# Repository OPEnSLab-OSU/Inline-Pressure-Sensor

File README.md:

# Inline-Pressure-Sensor

[Open Science Framework](https://osf.io/2mx4a/)

Code and hardware files for the inline pressure sensor

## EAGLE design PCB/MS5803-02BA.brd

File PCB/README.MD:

# PCB Files

This folder contains all the files that are necessary for ordering the PCB.

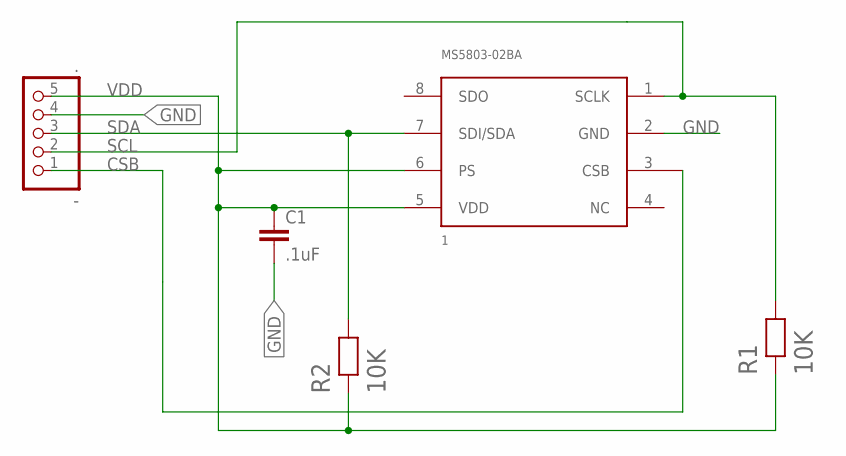
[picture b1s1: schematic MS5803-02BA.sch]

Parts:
-: .; 1X05
C1: .1uF; C0805
MS5803-02BA: 1; MS5803-02BA
R1, R2: 10K; 2012(0805)RESISTOR

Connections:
CSB: -.1, MS5803-02BA.3 (CSB)
GND: -.4, C1.2, MS5803-02BA.2 (GND)
SCL: -.2, MS5803-02BA.1 (SCLK), R1.2
SDA: -.3, MS5803-02BA.7 (SDI/SDA), R2.2
VDD: -.5, C1.1, MS5803-02BA.5 (VDD), MS5803-02BA.6 (PS), R1.1, R2.1

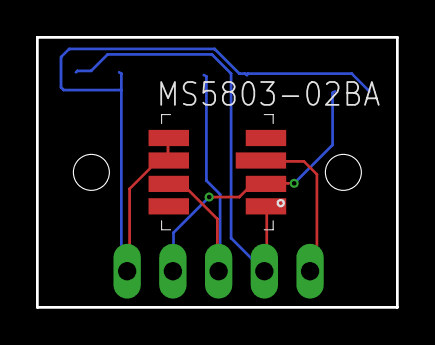
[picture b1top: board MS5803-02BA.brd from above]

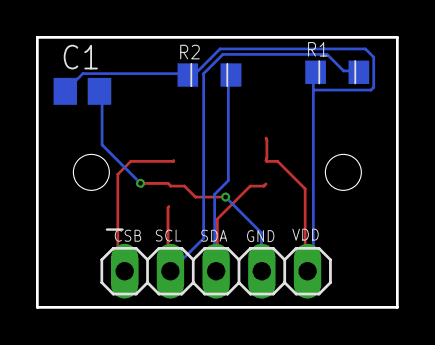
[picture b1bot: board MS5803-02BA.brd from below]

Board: 2 copper layers, 20.0 x 15.0 mm, 5 parts (4 on the bottom side), 5 nets.

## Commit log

2018-12-20 Added Loom instance code
2018-12-20 Added CAD and PCB folders
2018-12-20 Rename CAD files
2018-12-20 Added Loom support files for completeness
2018-12-20 Clean up .ino
2018-12-20 Update support files
2018-12-20 Added license
2018-12-20 Update readme with DOI badge
2019-01-03 Added copy of Serial RTC sync code
2019-01-05 Added link to OSF project
2019-01-23 Update .f3d parameter names
